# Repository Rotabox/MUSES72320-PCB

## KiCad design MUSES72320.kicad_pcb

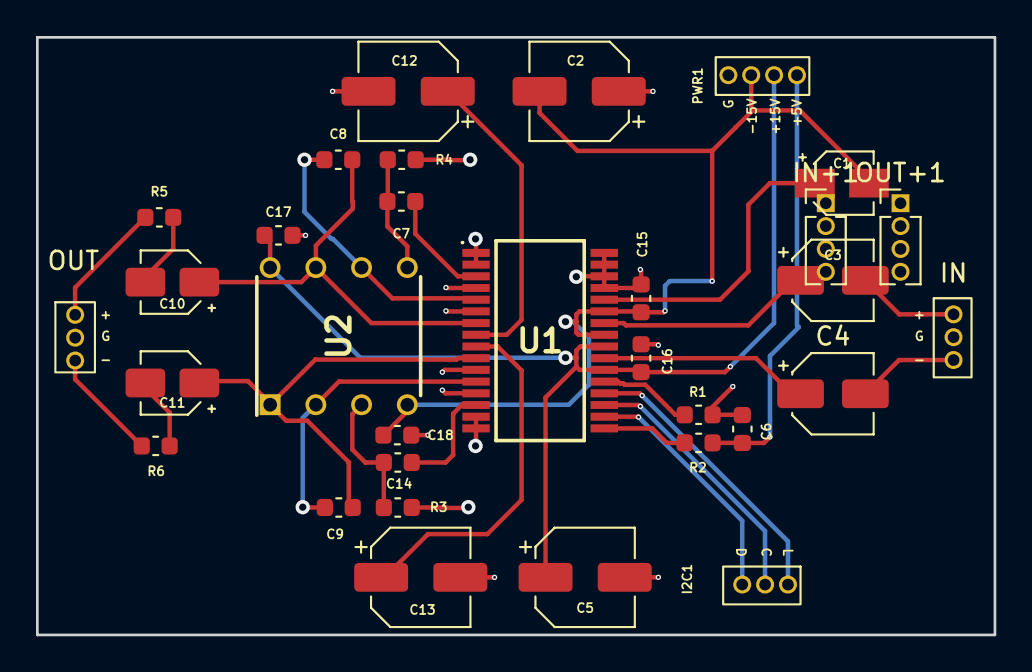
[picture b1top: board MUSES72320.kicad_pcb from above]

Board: 2 copper layers, 53.2 x 33.2 mm, 32 parts (0 on the bottom side), 28 nets.

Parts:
C1: 10uF; CP_Elec_3x5.3
C2, C5, C12, C13: 100uF; CP_Elec_5x5.3
C3, C4: 22uF; CP_Elec_4x5.3
C6: 1uF; C_0603_1608Metric
C7, C14: 10uF; C_0603_1608Metric
C8, C9: 10pF; C_0603_1608Metric
C10, C11: 10uF; CP_Elec_3x5.4
C15, C16, C17, C18: 0.1uF; C_0603_1608Metric
I2C1: Conn_01x04_Male; PinHeader_1x04_P1.27mm_Vertical
IN: Conn_01x04_Male; PinHeader_1x04_P1.27mm_Vertical
IN+1: Conn_01x04_Male; PinHeader_1x04_P1.27mm_Vertical
OUT: Conn_01x04_Male; PinHeader_1x04_P1.27mm_Vertical
OUT+1: Conn_01x04_Male; PinHeader_1x04_P1.27mm_Vertical
PWR1: PWR; PinHeader_1x04_P1.27mm_Vertical
R1, R2: 10K; C_0603_1608Metric
R3, R4: 470K; C_0603_1608Metric
R5, R6: 47R; C_0603_1608Metric
U1: MUSES72320V-TE2; SOP65P760X145-32N
U2: MUSES02; DIP762W56P254L880H425Q8N

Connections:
+5V: C6.2, PWR1.4, R2.2
+15V: C5.1, C16.2, C17.2, PWR1.3, U1.22 (V+_1), U1.24 (V+_2), U2.8 (V+)
-15V: C1.2, C2.2, C15.2, C18.1, PWR1.2, U1.25 (V-_1), U1.27 (V-_2), U2.4 (V-)
GNDPWR: C2.1, C5.2, C6.1, C12.2, C13.2, C15.1, C16.1, C17.1, C18.2, IN.2, OUT.2, R1.2, R3.2, R4.1, U1.1 (Z/C_REFL), U1.2 (L_REF_1), U1.4 (L_REF_2), U1.6 (L_REF_3), U1.11 (R_REF_1), U1.13 (R_REF_2), U1.15 (R_REF_3), U1.16 (Z/C_REFR), U1.29 (ADR2), U1.30 (ADR1), U1.31 (ADR0), U1.32 (Z/C)
unnamed: C1.1, U1.28 (D_CAP)
unnamed: C3.1, U1.26 (INL)
unnamed: C3.2, IN+1.1
unnamed: C4.1, U1.23 (INR)
unnamed: C4.2, IN.3, IN+1.3
unnamed: C7.1, U1.3 (L+)
unnamed: C7.2, R4.2, U2.5 (B_+INPUT)
unnamed: C8.1, U1.5 (L-), U2.6 (B_-INPUT)
unnamed: C9.1, U1.12 (R-), U2.2 (A_-INPUT)
unnamed: C8.2, C10.1, U1.7 (OUTL), U2.7 (B_OUTPUT)
unnamed: C10.2, R5.2
unnamed: C9.2, C11.1, U1.10 (OUTR), U2.1 (A_OUTPUT)
unnamed: C11.2, R6.2
unnamed: C12.1, U1.8 (DCCAP_L)
unnamed: C13.1, U1.9 (DCCAP_R)
unnamed: C14.1, U1.14 (R+)
unnamed: C14.2, R3.1, U2.3 (A_+INPUT)
unnamed: I2C1.2, U1.19 (CLOCK)
unnamed: I2C1.3, U1.18 (DATA)
unnamed: I2C1.1, U1.20 (LATCH)
unnamed: OUT.1, OUT+1.1, R5.1
unnamed: OUT.3, OUT+1.3, R6.1
unnamed: R1.1, U1.21 (D_REF)
unnamed: R2.1, U1.17 (D_VDD)

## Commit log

2023-05-25 MUSES72320-PCB Update
